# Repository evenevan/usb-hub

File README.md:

# usb-hub

KiCad design files for a USB hub based on the LAN9512, offering 2x USB A and an Ethernet port

See https://evanfeng.dev/blog/usb-hub

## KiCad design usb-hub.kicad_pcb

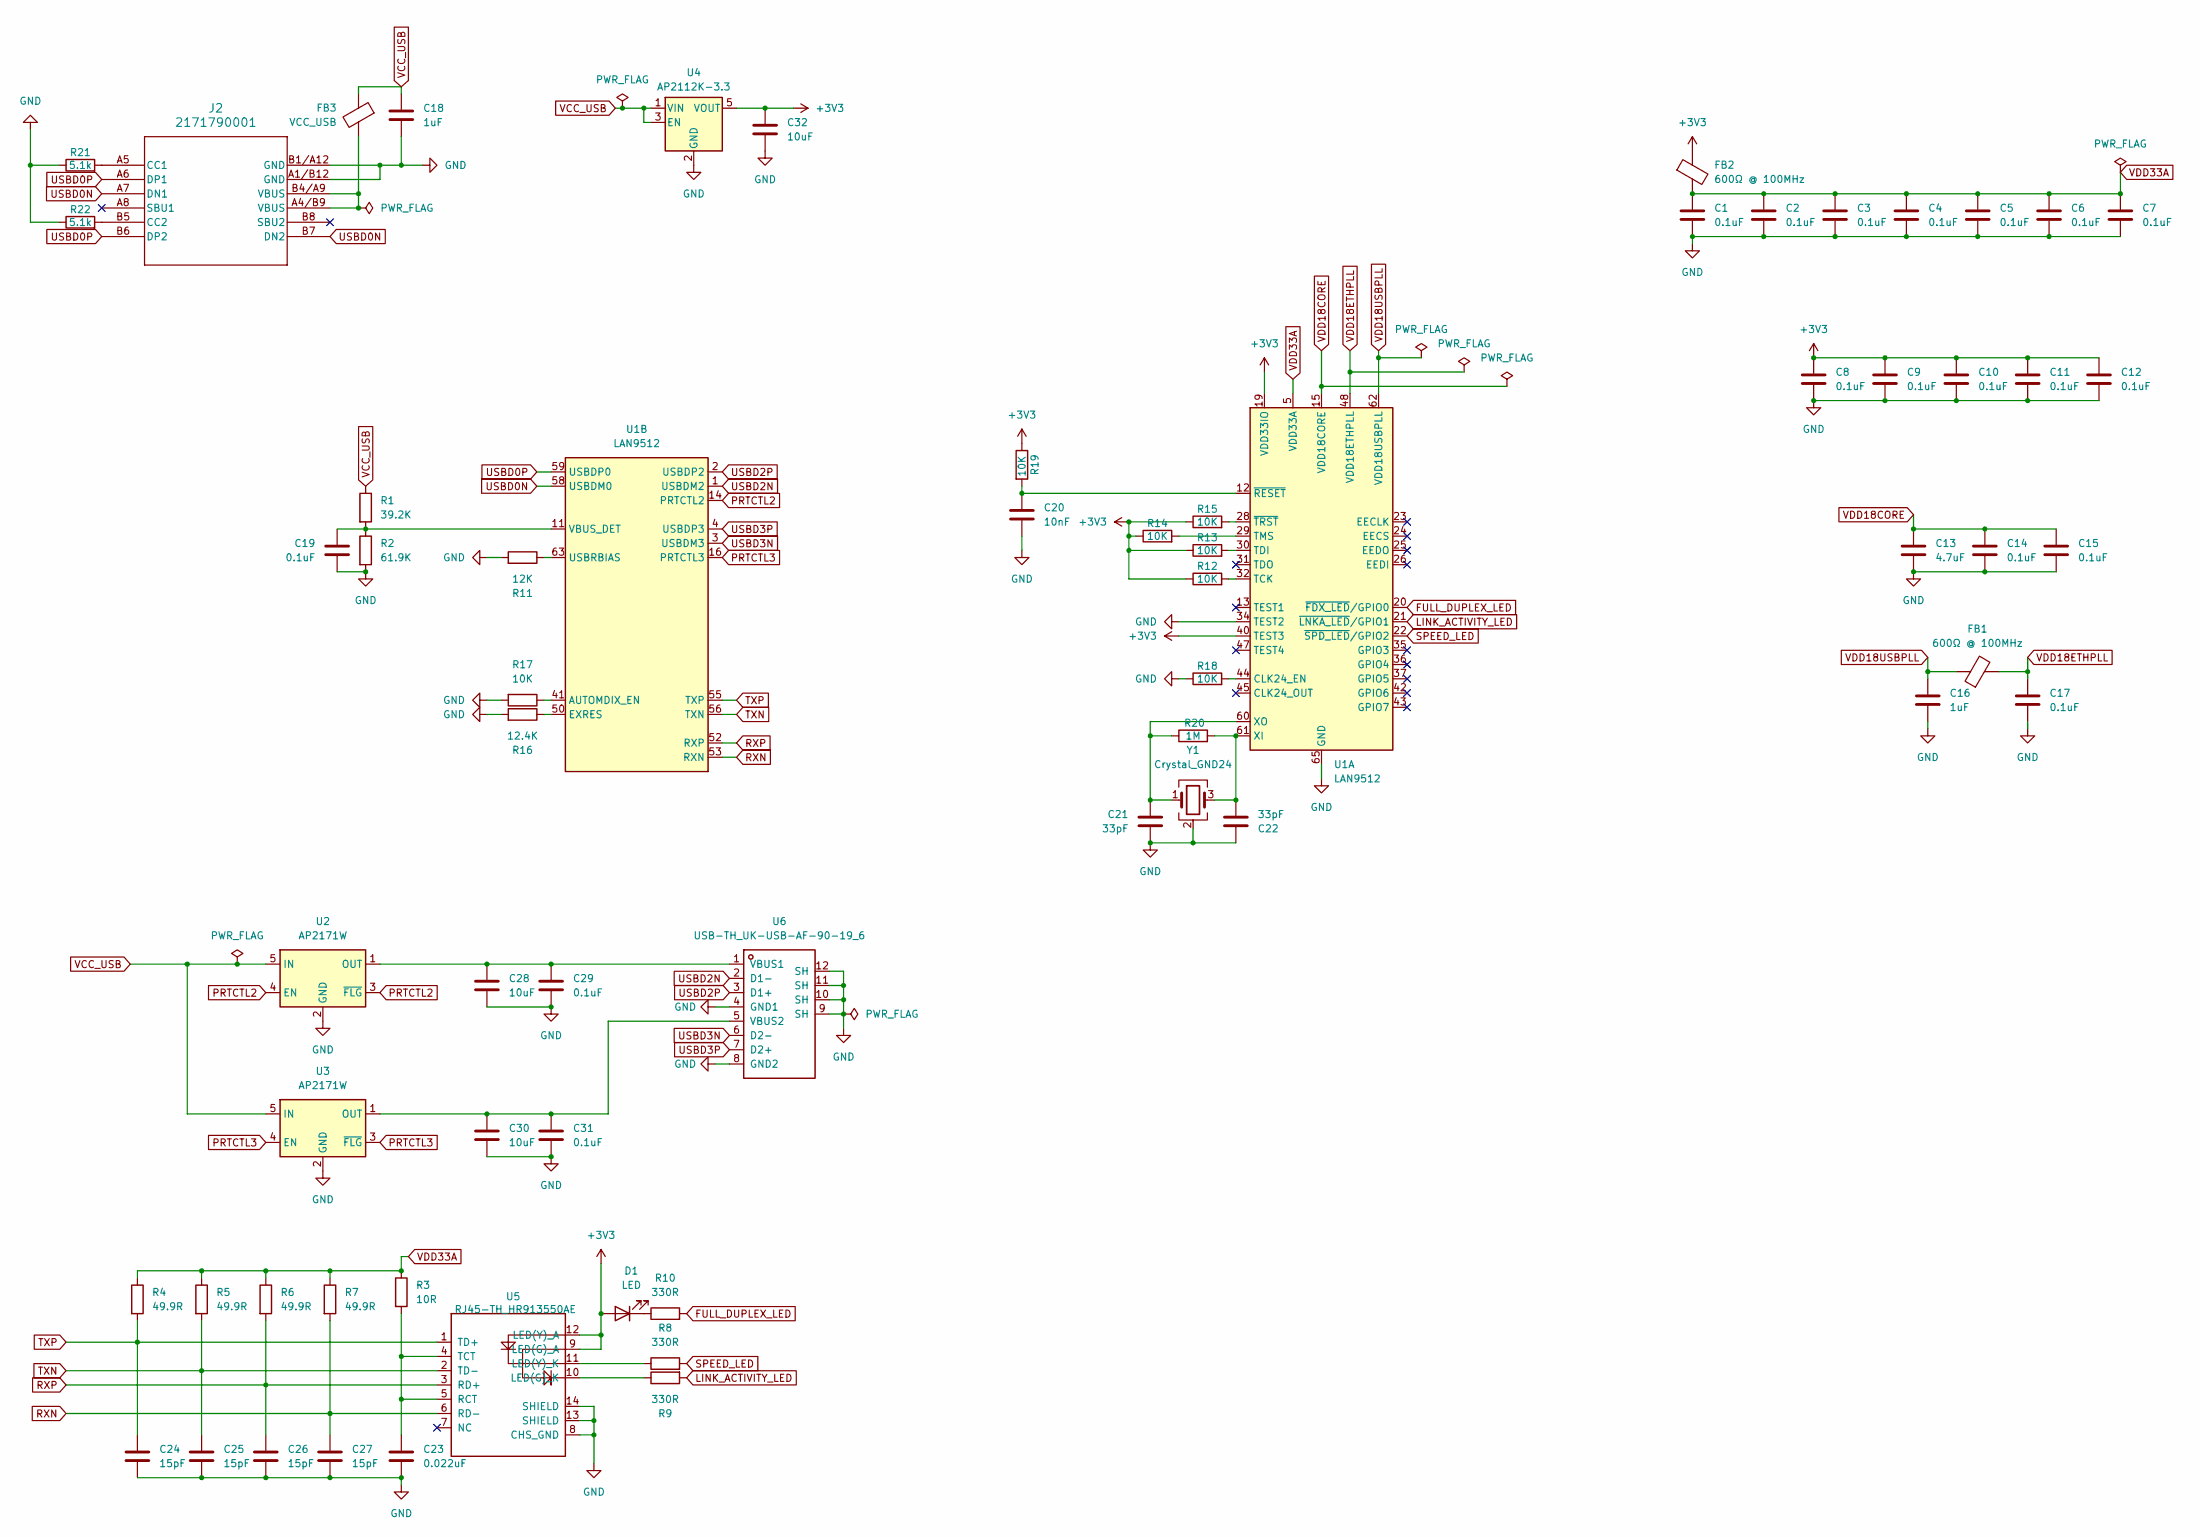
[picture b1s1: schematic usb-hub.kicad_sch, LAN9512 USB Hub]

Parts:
C1, C2, C3, C4, C5, C6, C7, C8, C9, C10, C11, C12: 0.1uF; C_0805_2012Metric_Pad1.18x1.45mm_HandSolder
C13: 4.7uF; C_0805_2012Metric
C14, C15, C17, C19, C29, C31: 0.1uF; C_0603_1608Metric
C16, C18: 1uF; C_0603_1608Metric
C20: 10nF; C_0603_1608Metric
C21, C22: 33pF; C_0603_1608Metric
C23: 0.022uF; C_0603_1608Metric
C24, C25, C26, C27: 15pF; C_0603_1608Metric
C28, C30, C32: 10uF; C_0805_2012Metric
D1: LED; LED_0603_1608Metric
FB1, FB2: 600Ω @ 100MHz; L_0603_1608Metric
FB3: VCC_USB; L_0603_1608Metric
J2: 2171790001; 2171790001_MOL
R1: 39.2K; R_0603_1608Metric
R2: 61.9K; R_0603_1608Metric
R3: 10R; R_0603_1608Metric
R4, R5, R6, R7: 49.9R; R_0603_1608Metric
R8, R9, R10: 330R; R_0603_1608Metric
R11: 12K; R_0603_1608Metric
R12, R13, R14, R15, R17, R18, R19: 10K; R_0603_1608Metric
R16: 12.4K; R_0603_1608Metric
R20: 1M; R_0603_1608Metric
R21, R22: 5.1k; R_0603_1608Metric
U1: LAN9512; QFN-64-1EP_9x9mm_P0.5mm_EP7.3x7.3mm
U2, U3: AP2171W; SOT-23-5
U4: AP2112K-3.3; SOT-23-5
U5: RJ45-TH_HR913550AE; RJ45-TH_HR913550AE_HR913550AE_C192706
U6: USB-TH_UK-USB-AF-90-19_6; USB-TH_UK-USB-AF-90-19_6_UK-USB_AF_90-19_6_C698206
Y1: Crystal_GND24; Crystal_SMD_3225-4Pin_3.2x2.5mm

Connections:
+3V3: C8.2, C9.2, C10.2, C11.2, C12.2, C32.1, D1.2 (A), FB2.1, R12.1, R13.1, R14.1, R15.1, R19.1, U1.19 (VDD33IO), U1.27 (VDD33IO), U1.33 (VDD33IO), U1.39 (VDD33IO), U1.40 (TEST3), U1.46 (VDD33IO), U4.5 (VOUT), U5.9 (LED(G)_A), U5.12 (LED(Y)_A)
FULL_DUPLEX_LED: R10.2, U1.20 (~FDX_LED/GPIO0)
GND: C1.1, C2.1, C3.1, C4.1, C5.1, C6.1, C7.1, C8.1, C9.1, C10.1, C11.1, C12.1, C13.2, C14.1, C15.1, C16.2, C17.2, C18.2, C19.2, C20.2, C21.2, C22.1, C23.2, C24.2, C25.2, C26.2, C27.2, C28.2, C29.2, C30.2, C31.2, C32.2, J2.A1/B12 (GND), J2.B1/A12 (GND), R2.2, R11.2, R16.2, R17.2, R18.1, R21.1, R22.1, U1.34 (TEST2), U1.65 (GND), U2.2 (GND), U3.2 (GND), U4.2 (GND), U5.8 (CHS_GND), U5.13 (SHIELD), U5.14 (SHIELD), U6.4 (GND1), U6.8 (GND2), U6.9 (SH), U6.10 (SH), U6.11 (SH), U6.12 (SH), Y1.2 (G), Y1.4 (G)
LINK_ACTIVITY_LED: R9.2, U1.21 (~LNKA_LED/GPIO1)
unnamed: D1.1 (K), R10.1
unnamed: FB3.2, J2.A4/B9 (VBUS), J2.B4/A9 (VBUS)
unnamed: J2.A5 (CC1), R21.2
unnamed: J2.B5 (CC2), R22.2
unnamed: R18.2, U1.44 (CLK24_EN)
unnamed: R12.2, U1.32 (TCK)
unnamed: R13.2, U1.30 (TDI)
unnamed: R14.2, U1.29 (TMS)
unnamed: C22.2, R20.2, U1.61 (XI), Y1.3
unnamed: C21.1, R20.1, U1.60 (XO), Y1.1
unnamed: C20.1, R19.2, U1.12 (~RESET)
unnamed: R15.2, U1.28 (~TRST)
unnamed: R17.1, U1.41 (AUTOMDIX_EN)
unnamed: R16.1, U1.50 (EXRES)
unnamed: R11.1, U1.63 (USBRBIAS)
unnamed: C19.1, R1.2, R2.1, U1.11 (VBUS_DET)
unnamed: C28.1, C29.1, U2.1 (OUT), U6.1 (VBUS1)
unnamed: C30.1, C31.1, U3.1 (OUT), U6.5 (VBUS2)
unnamed: R9.1, U5.10 (LED(G)_K)
unnamed: R8.1, U5.11 (LED(Y)_K)
unnamed: C23.1, R3.2, U5.4 (TCT), U5.5 (RCT)
PRTCTL2: U1.14 (PRTCTL2), U2.3 (~FLG), U2.4 (EN)
PRTCTL3: U1.16 (PRTCTL3), U3.3 (~FLG), U3.4 (EN)
RXN: C27.1, R7.2, U1.53 (RXN), U5.6 (RD-)
RXP: C26.1, R6.2, U1.52 (RXP), U5.3 (RD+)
SPEED_LED: R8.2, U1.22 (~SPD_LED/GPIO2)
TXN: C25.1, R5.2, U1.56 (TXN), U5.2 (TD-)
TXP: C24.1, R4.2, U1.55 (TXP), U5.1 (TD+)
USBD0N: J2.A7 (DN1), J2.B7 (DN2), U1.58 (USBDM0)
USBD0P: J2.A6 (DP1), J2.B6 (DP2), U1.59 (USBDP0)
USBD2N: U1.1 (USBDM2), U6.2 (D1-)
USBD2P: U1.2 (USBDP2), U6.3 (D1+)
USBD3N: U1.3 (USBDM3), U6.6 (D2-)
USBD3P: U1.4 (USBDP3), U6.7 (D2+)
VCC_USB: C18.1, FB3.1, R1.1, U2.5 (IN), U3.5 (IN), U4.1 (VIN), U4.3 (EN)
VDD18CORE: C13.1, C14.2, C15.2, U1.15 (VDD18CORE), U1.38 (VDD18CORE)
VDD18ETHPLL: C17.1, FB1.2, U1.48 (VDD18ETHPLL)
VDD18USBPLL: C16.1, FB1.1, U1.62 (VDD18USBPLL)
VDD33A: C1.2, C2.2, C3.2, C4.2, C5.2, C6.2, C7.2, FB2.2, R3.1, R4.1, R5.1, R6.1, R7.1, U1.5 (VDD33A), U1.10 (VDD33A), U1.49 (VDD33A), U1.51 (VDD33A), U1.54 (VDD33A), U1.57 (VDD33A), U1.64 (VDD33A)

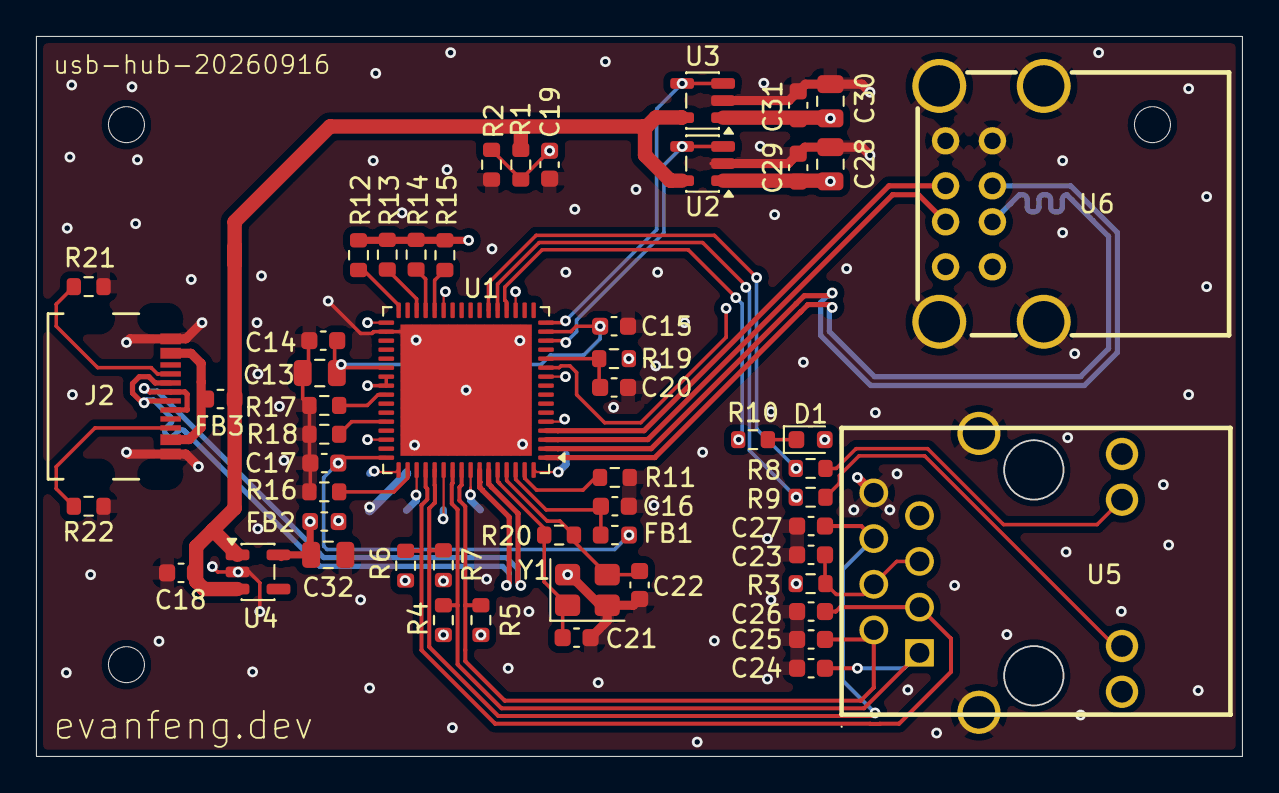
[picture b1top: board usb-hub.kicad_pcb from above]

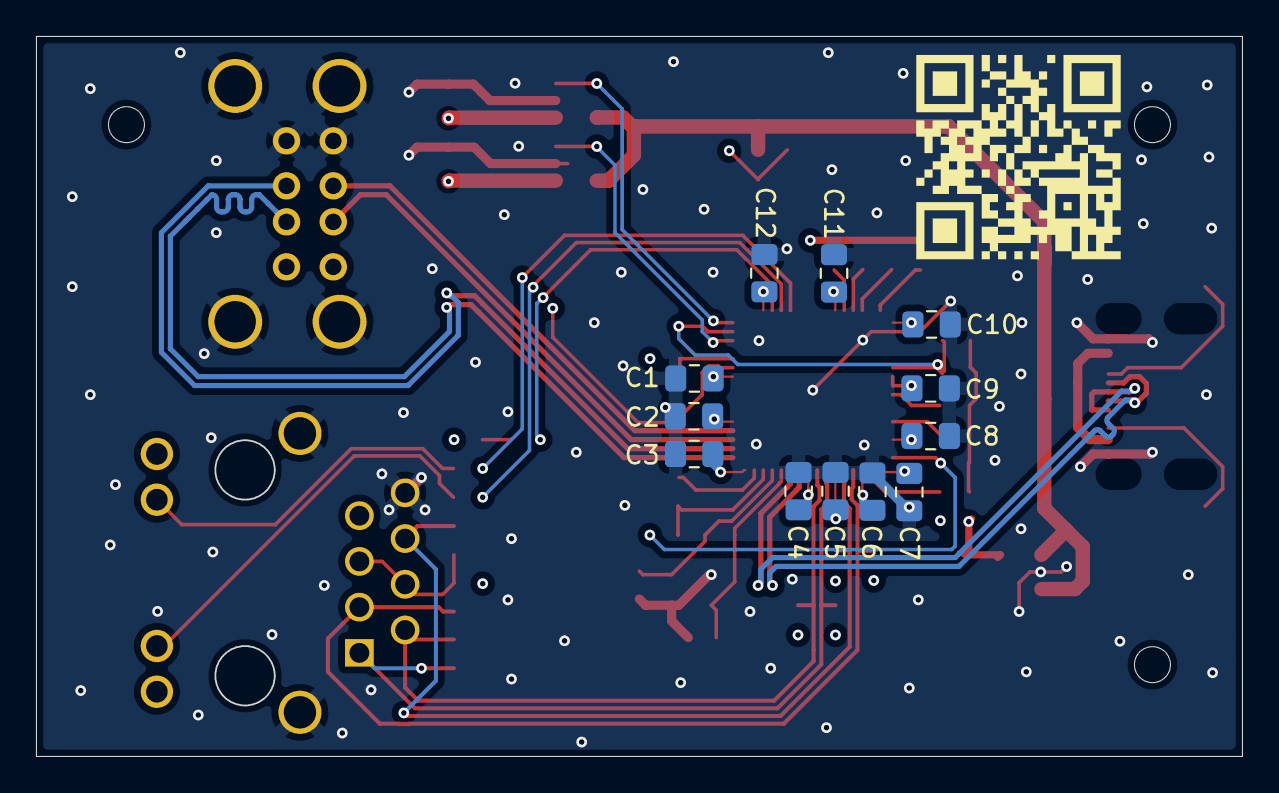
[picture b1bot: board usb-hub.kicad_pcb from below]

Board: 4 copper layers, 67.0 x 40.0 mm, 66 parts (12 on the bottom side), 43 nets.

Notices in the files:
usb-hub.kicad_sch:
Copyright (C) Evan Feng
https://www.gnu.org/licenses/gpl-3.0.en.html
GNU General Public License version 3
